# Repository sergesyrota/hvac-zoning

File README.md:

# HVAC Zoning

System to segment single hvac unit into multiple zones

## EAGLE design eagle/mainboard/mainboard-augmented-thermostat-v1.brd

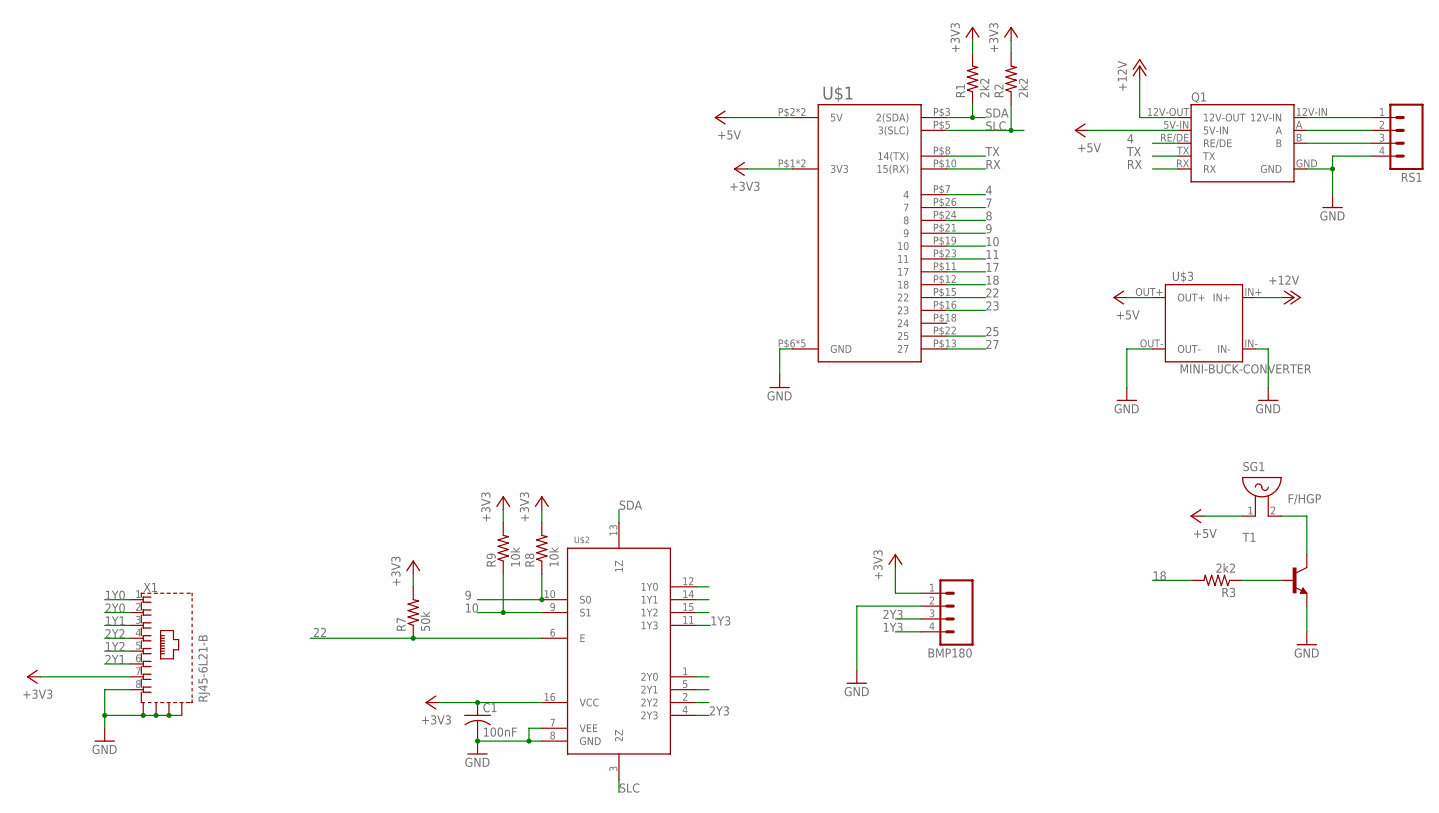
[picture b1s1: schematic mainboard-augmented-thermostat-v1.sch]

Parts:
BMP180: M04; 04P
C1: 100nF; C0603K
Q1: RS485-ADAPTER0.05-CONNECTOR; RS485-ADAPTOR-05
R1, R2, R3: 2k2; R0603
R7: 50k; R0603
R8, R9: 10k; R0603
RS1: M04; 04P
SG1: F/HGP
T1: BC808-NPN-SOT23-BEC; SOT23-BEC
U$1: RASPI-GPIO; RASPI-GPIO-1
U$2: 74HC4052SO-16; SO16
U$3: MINI-BUCK-CONVERTER
X1: RJ45-6L21-B; RJ45-SHIELD1

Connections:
1Y0: U$2.12 (1Y0), X1.1
1Y1: U$2.14 (1Y1), X1.3
1Y2: U$2.15 (1Y2), X1.5
1Y3: BMP180.4, U$2.11 (1Y3)
2Y0: U$2.1 (2Y0), X1.2
2Y1: U$2.5 (2Y1), X1.6
2Y2: U$2.2 (2Y2), X1.4
2Y3: BMP180.3, U$2.4 (2Y3)
4: Q1.RE/DE, U$1.P$7 (4)
7: U$1.P$26 (7)
8: U$1.P$24 (8)
9: R8.1, U$1.P$21 (9), U$2.10 (S0)
10: R9.1, U$1.P$19 (10), U$2.9 (S1)
11: U$1.P$23 (11)
17: U$1.P$11 (17)
18: R3.2, U$1.P$12 (18)
22: R7.1, U$1.P$15 (22), U$2.6 (E)
23: U$1.P$16 (23)
25: U$1.P$22 (25)
27: U$1.P$13 (27)
+3V3: BMP180.1, C1.1, R1.2, R2.2, R7.2, R8.2, R9.2, U$1.P$1 (3V3), U$1.P$17 (3V3), U$2.16 (VCC), X1.7
+5V: Q1.5V-IN, SG1.1, U$1.P$2 (5V), U$1.P$4 (5V), U$3.OUT+
+12V: Q1.12V-OUT, U$3.IN+
GND: BMP180.2, C1.2, Q1.GND, RS1.4, T1.E, U$1.P$6 (GND), U$1.P$9 (GND), U$1.P$14 (GND), U$1.P$20 (GND), U$1.P$25 (GND), U$2.7 (VEE), U$2.8 (GND), U$3.IN-, U$3.OUT-, X1.8, X1.S1 (S), X1.S2 (S), X1.S3 (S), X1.S4 (S)
unnamed: R3.1, T1.B
unnamed: SG1.2, T1.C
RS-12V: Q1.12V-IN, RS1.1
RS-A: Q1.A, RS1.2
RS-B: Q1.B, RS1.3
RX: Q1.RX, U$1.P$10 (15(RX))
SDA: R1.1, U$1.P$3 (2(SDA)), U$2.13 (1Z)
SLC: R2.1, U$1.P$5 (3(SLC)), U$2.3 (2Z)
TX: Q1.TX, U$1.P$8 (14(TX))

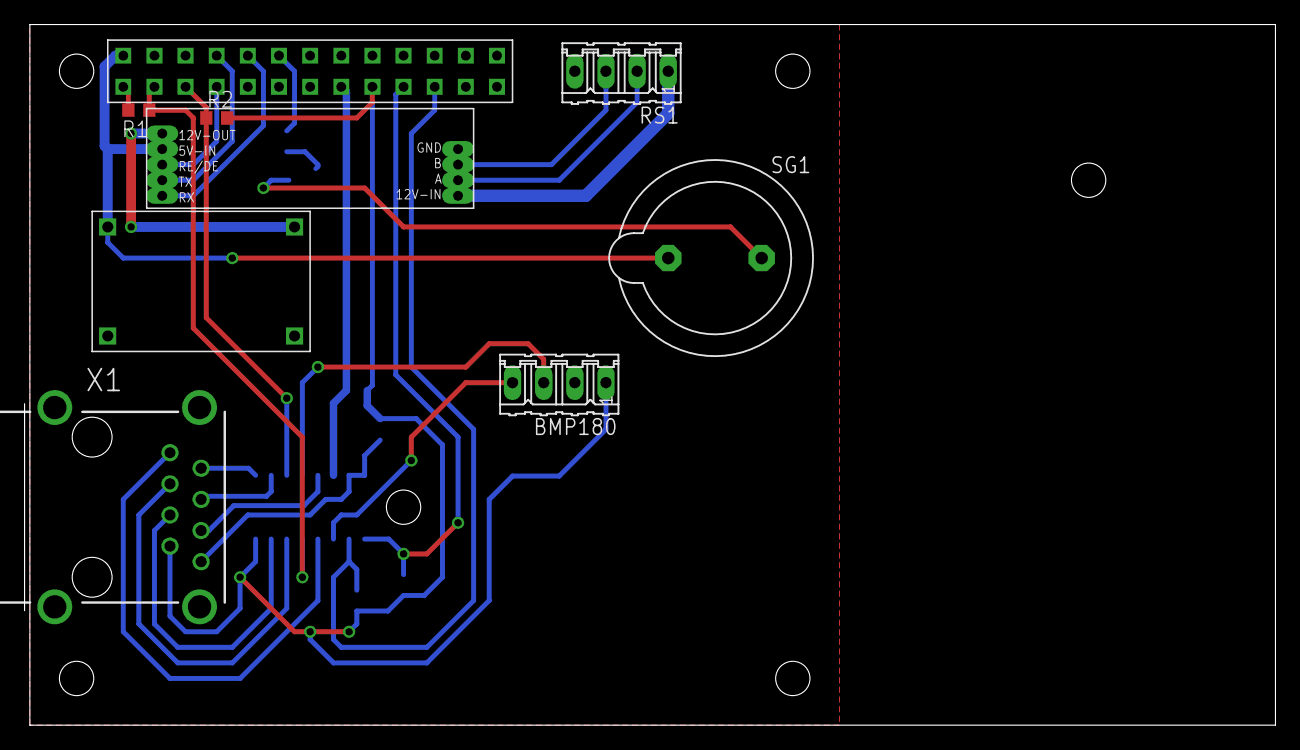
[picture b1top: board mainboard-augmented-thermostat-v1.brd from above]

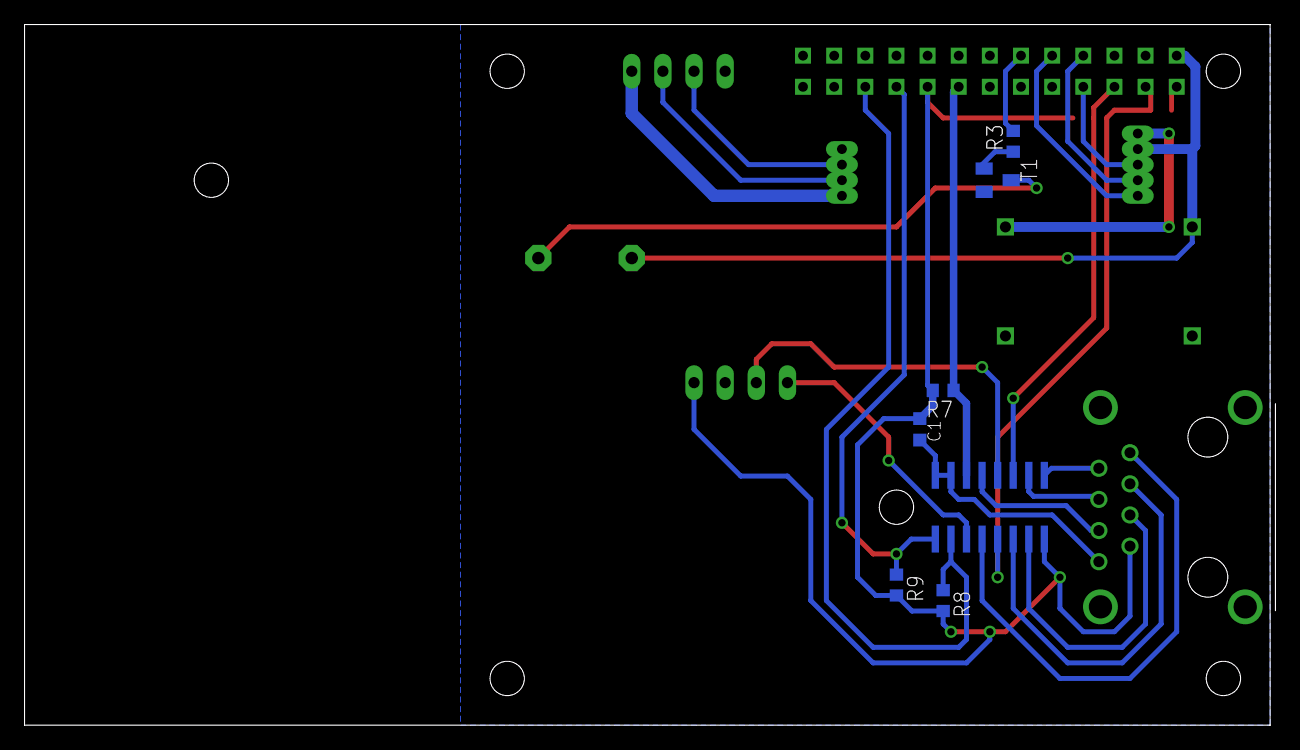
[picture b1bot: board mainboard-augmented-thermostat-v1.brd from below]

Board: 2 copper layers, 102.0 x 57.1 mm, 16 parts (7 on the bottom side), 26 nets.

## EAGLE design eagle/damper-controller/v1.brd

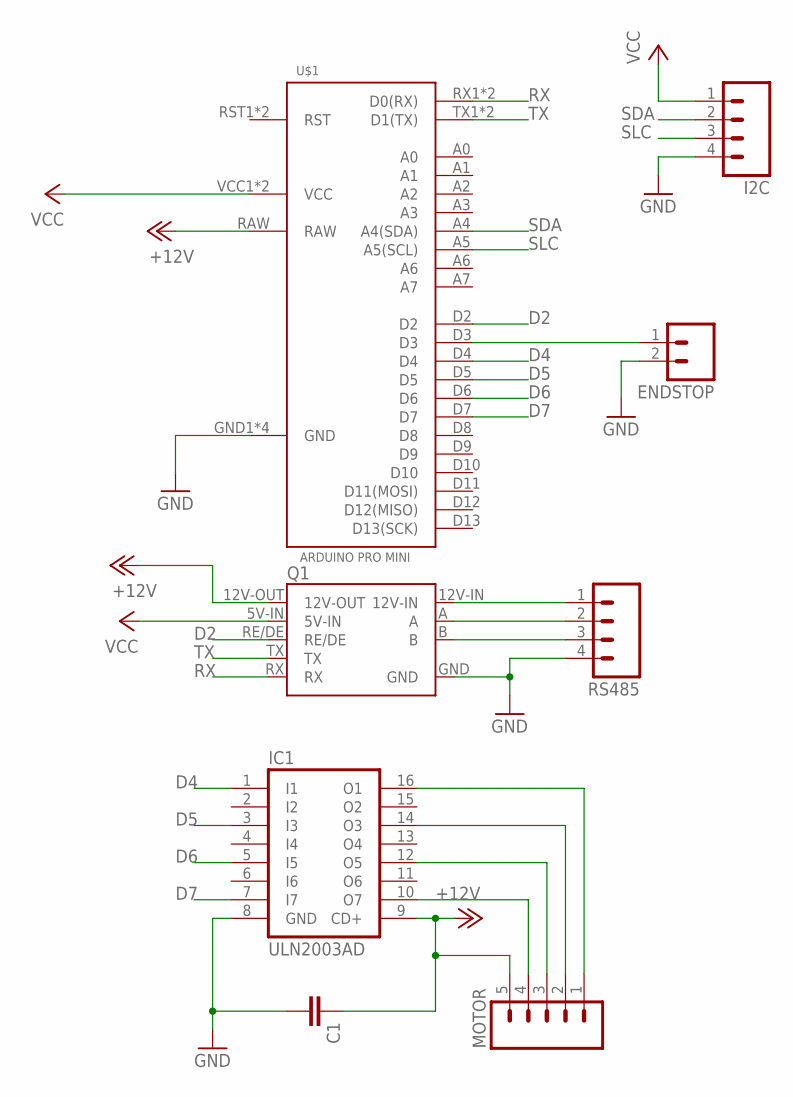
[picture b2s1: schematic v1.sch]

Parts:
C1: CC0603; C0603
ENDSTOP: M02; 02P
I2C: M04; 04P
IC1: ULN2003AD; SO16
MOTOR: M05; 05P
Q1: RS485-ADAPTER0.05-CONNECTOR; RS485-ADAPTOR-05
RS485: M04; 04P
U$1: ARDUINO-PRO-MINI

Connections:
+12V: C1.1, IC1.9 (CD+), MOTOR.5, Q1.12V-OUT, U$1.RAW
D2: Q1.RE/DE, U$1.D2
D4: IC1.1 (I1), U$1.D4
D5: IC1.3 (I3), U$1.D5
D6: IC1.5 (I5), U$1.D6
D7: IC1.7 (I7), U$1.D7
GND: C1.2, ENDSTOP.2, I2C.4, IC1.8 (GND), Q1.GND, RS485.4, U$1.GND1 (GND), U$1.GND2 (GND), U$1.GND3 (GND), U$1.GND4 (GND)
unnamed: Q1.12V-IN, RS485.1
unnamed: IC1.16 (O1), MOTOR.1
unnamed: IC1.14 (O3), MOTOR.2
unnamed: IC1.12 (O5), MOTOR.3
unnamed: IC1.10 (O7), MOTOR.4
unnamed: Q1.A, RS485.2
unnamed: Q1.B, RS485.3
unnamed: ENDSTOP.1, U$1.D3
RX: Q1.RX, U$1.RX1 (D0(RX)), U$1.RX2 (D0(RX))
SDA: I2C.2, U$1.A4 (A4(SDA))
SLC: I2C.3, U$1.A5 (A5(SCL))
TX: Q1.TX, U$1.TX1 (D1(TX)), U$1.TX2 (D1(TX))
VCC: I2C.1, Q1.5V-IN, U$1.VCC1 (VCC), U$1.VCC2 (VCC)

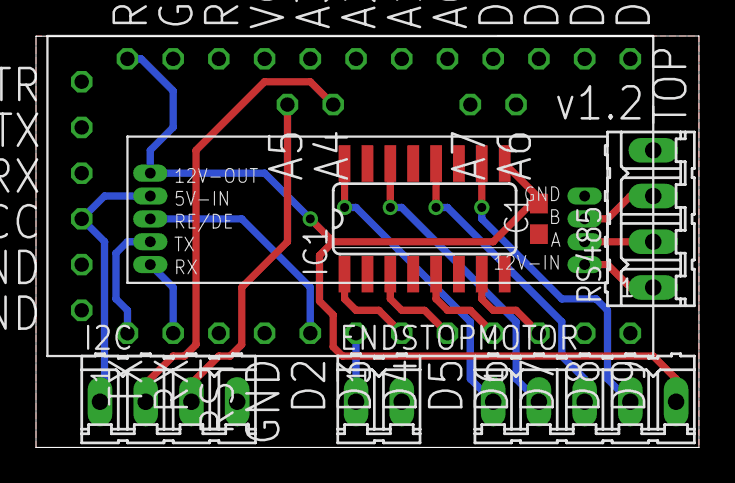
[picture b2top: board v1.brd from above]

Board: 2 copper layers, 36.8 x 22.9 mm, 8 parts (0 on the bottom side), 20 nets.

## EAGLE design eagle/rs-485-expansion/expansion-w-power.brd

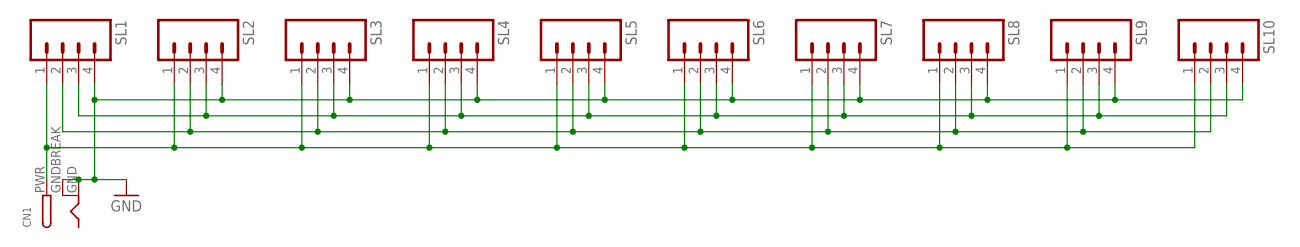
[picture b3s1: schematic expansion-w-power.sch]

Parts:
CN1: DCBARRELPTH; DCJACK_2MM_PTH
SL1, SL2, SL3, SL4, SL5, SL6, SL7, SL8, SL9, SL10: M04; 04P

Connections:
GND: CN1.GND, CN1.GNDBREAK, SL1.4, SL2.4, SL3.4, SL4.4, SL5.4, SL6.4, SL7.4, SL8.4, SL9.4, SL10.4
unnamed: SL1.3, SL2.3, SL3.3, SL4.3, SL5.3, SL6.3, SL7.3, SL8.3, SL9.3, SL10.3
unnamed: SL1.2, SL2.2, SL3.2, SL4.2, SL5.2, SL6.2, SL7.2, SL8.2, SL9.2, SL10.2
unnamed: CN1.PWR, SL1.1, SL2.1, SL3.1, SL4.1, SL5.1, SL6.1, SL7.1, SL8.1, SL9.1, SL10.1

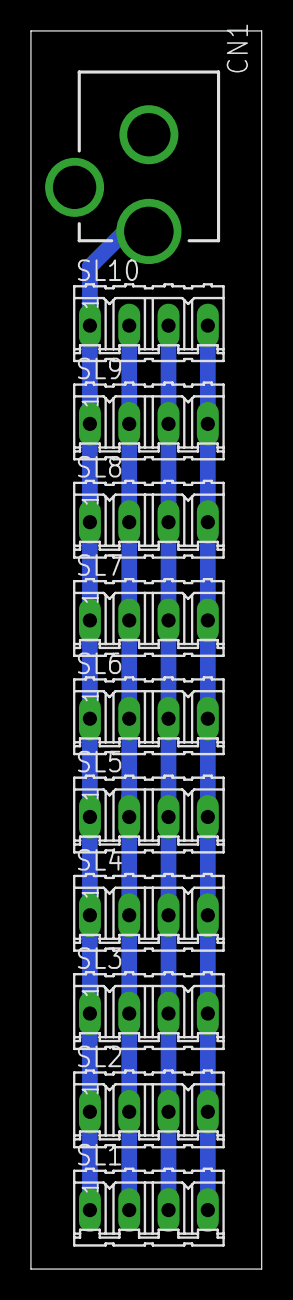
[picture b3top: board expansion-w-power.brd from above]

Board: 2 copper layers, 14.9 x 80.0 mm, 11 parts (0 on the bottom side), 4 nets.

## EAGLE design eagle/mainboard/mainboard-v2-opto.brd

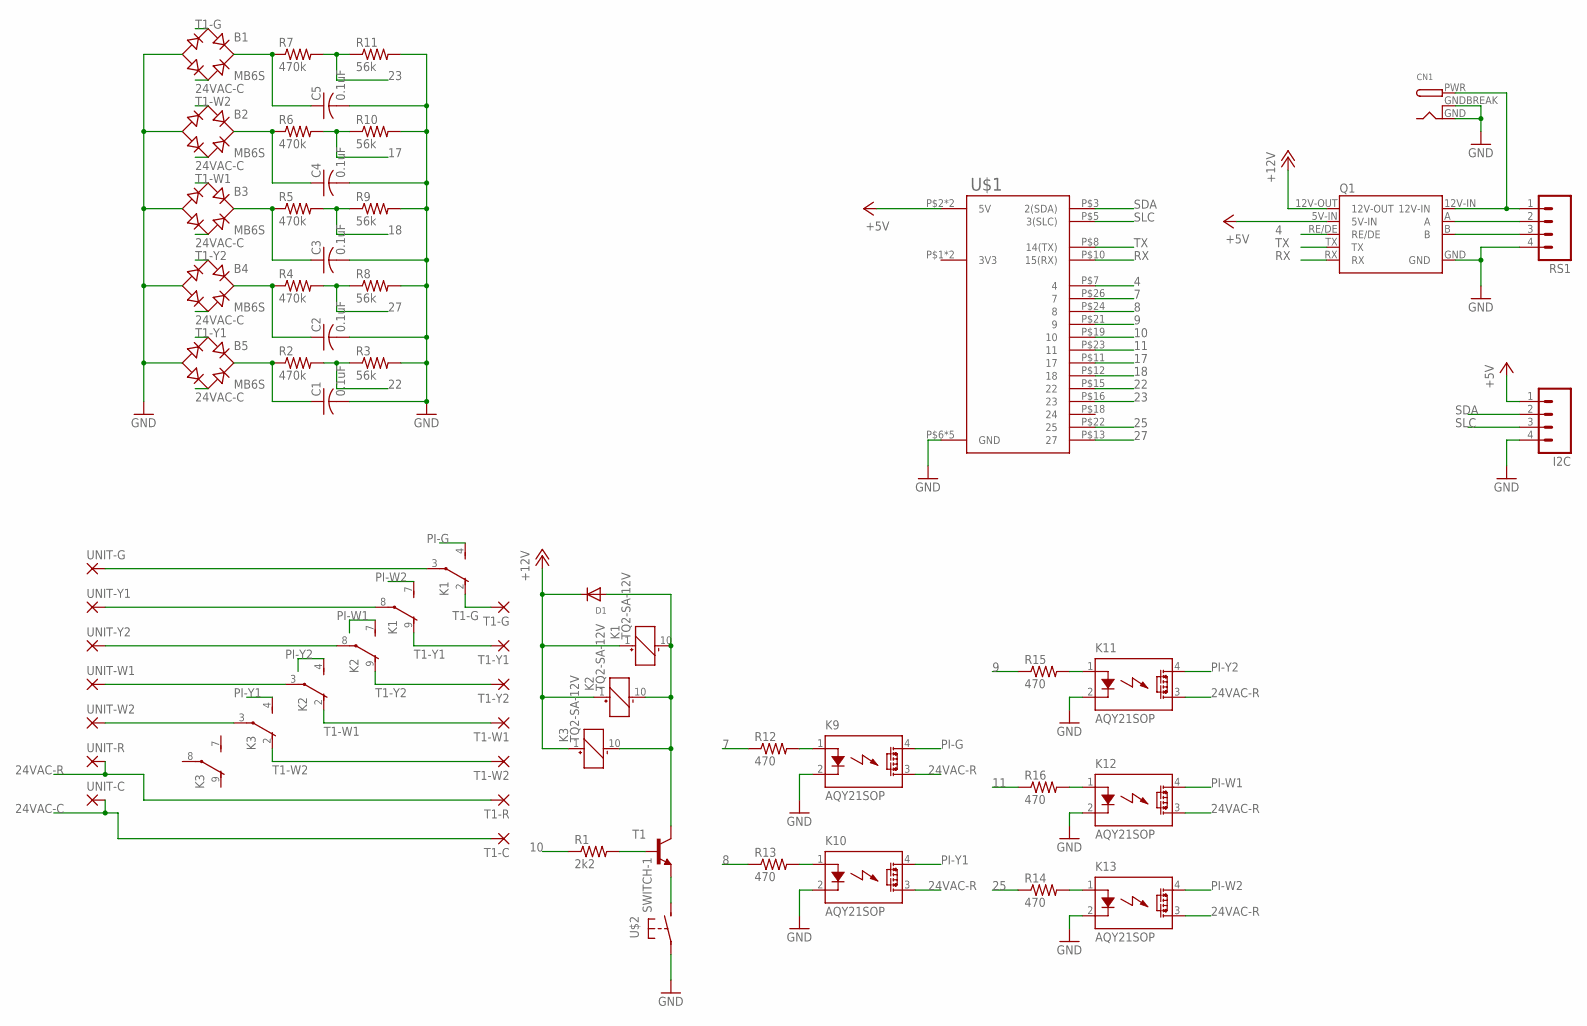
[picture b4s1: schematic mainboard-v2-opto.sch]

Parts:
B1, B2, B3, B4, B5: MB6S; SOIC-4
C1, C2, C3, C4, C5: 0.1uF; C0603
CN1: DCBARRELPTH; DCJACK_2MM_PTH
D1: DIODESMA; SMADIODE
I2C: M04; 04P
K1, K2, K3: TQ2-SA-12V; TQ-SA
K9, K10, K11, K12, K13: AQY21SOP; SOP04
Q1: RS485-ADAPTER0.05-CONNECTOR; RS485-ADAPTOR-05
R1: 2k2; R0603
R2, R4, R5, R6, R7: 470k; R0603
R3, R8, R9, R10, R11: 56k; R0603
R12, R13, R14, R15, R16: 470; R0603
RS1: M04; 04P
T1: BC808-NPN-SOT23-BEC; SOT23-BEC
T1-C, T1-G, T1-R, T1-W1, T1-W2, T1-Y1, T1-Y2: 2,15/1,0
U$1: RASPI-GPIO; RASPI-GPIO-1
U$2: SWITCH-1
UNIT-C: 2,15/1,0
UNIT-G: 2,15/1,0
UNIT-R: 2,15/1,0
UNIT-W1, UNIT-W2: 2,15/1,0
UNIT-Y1, UNIT-Y2: 2,15/1,0

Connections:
3V3: U$1.P$1 (3V3), U$1.P$17 (3V3)
4: Q1.RE/DE, U$1.P$7 (4)
7: R12.1, U$1.P$26 (7)
8: R13.1, U$1.P$24 (8)
9: R15.1, U$1.P$21 (9)
10: R1.1, U$1.P$19 (10)
11: R16.1, U$1.P$23 (11)
17: R6.2, R10.1, U$1.P$11 (17)
18: R5.2, R9.1, U$1.P$12 (18)
22: R2.2, R3.1, U$1.P$15 (22)
23: R7.2, R11.1, U$1.P$16 (23)
24VAC-C: B1.~2 (AC2), B2.~2 (AC2), B3.~2 (AC2), B4.~2 (AC2), B5.~2 (AC2), T1-C.1, UNIT-C.1
24VAC-R: K9.3 (DS2), K10.3 (DS2), K11.3 (DS2), K12.3 (DS2), K13.3 (DS2), T1-R.1, UNIT-R.1
25: R14.1, U$1.P$22 (25)
27: R4.2, R8.1, U$1.P$13 (27)
+5V: I2C.1, Q1.5V-IN, U$1.P$2 (5V), U$1.P$4 (5V)
+12V: D1.C, K1.1 (+), K2.1 (+), K3.1 (+), Q1.12V-OUT
GND: B1.-, B2.-, B3.-, B4.-, B5.-, C1.2, C2.2, C3.2, C4.2, C5.2, CN1.GND, CN1.GNDBREAK, I2C.4, K9.2 (K), K10.2 (K), K11.2 (K), K12.2 (K), K13.2 (K), Q1.GND, R3.2, R8.2, R9.2, R10.2, R11.2, RS1.4, U$1.P$6 (GND), U$1.P$9 (GND), U$1.P$14 (GND), U$1.P$20 (GND), U$1.P$25 (GND), U$2.P$1
unnamed: B5.+, C1.1, R2.1
unnamed: K1.3, UNIT-G.1
unnamed: K1.8, UNIT-Y1.1
unnamed: K2.8, UNIT-Y2.1
unnamed: D1.A, K1.10 (-), K2.10 (-), K3.10 (-), T1.C
unnamed: R1.2, T1.B
unnamed: K2.3, UNIT-W1.1
unnamed: K13.1 (A), R14.2
unnamed: K3.3, UNIT-W2.1
unnamed: B1.+, C5.1, R7.1
unnamed: K12.1 (A), R16.2
unnamed: K11.1 (A), R15.2
unnamed: B4.+, C2.1, R4.1
unnamed: B3.+, C3.1, R5.1
unnamed: T1.E, U$2.P$2 (S)
unnamed: K9.1 (A), R12.2
unnamed: K10.1 (A), R13.2
unnamed: B2.+, C4.1, R6.1
PI-G: K1.4 (S), K9.4 (DS1)
PI-W1: K2.7 (S), K12.4 (DS1)
PI-W2: K1.7 (S), K13.4 (DS1)
PI-Y1: K3.4 (S), K10.4 (DS1)
PI-Y2: K2.4 (S), K11.4 (DS1)
RS-12V: CN1.PWR, Q1.12V-IN, RS1.1
RS-A: Q1.A, RS1.2
RS-B: Q1.B, RS1.3
RX: Q1.RX, U$1.P$10 (15(RX))
SDA: I2C.2, U$1.P$3 (2(SDA))
SLC: I2C.3, U$1.P$5 (3(SLC))
T1-G: B1.~1 (AC1), K1.2 (O), T1-G.1
T1-W1: B3.~1 (AC1), K2.2 (O), T1-W1.1
T1-W2: B2.~1 (AC1), K3.2 (O), T1-W2.1
T1-Y1: B5.~1 (AC1), K1.9 (O), T1-Y1.1
T1-Y2: B4.~1 (AC1), K2.9 (O), T1-Y2.1
TX: Q1.TX, U$1.P$8 (14(TX))

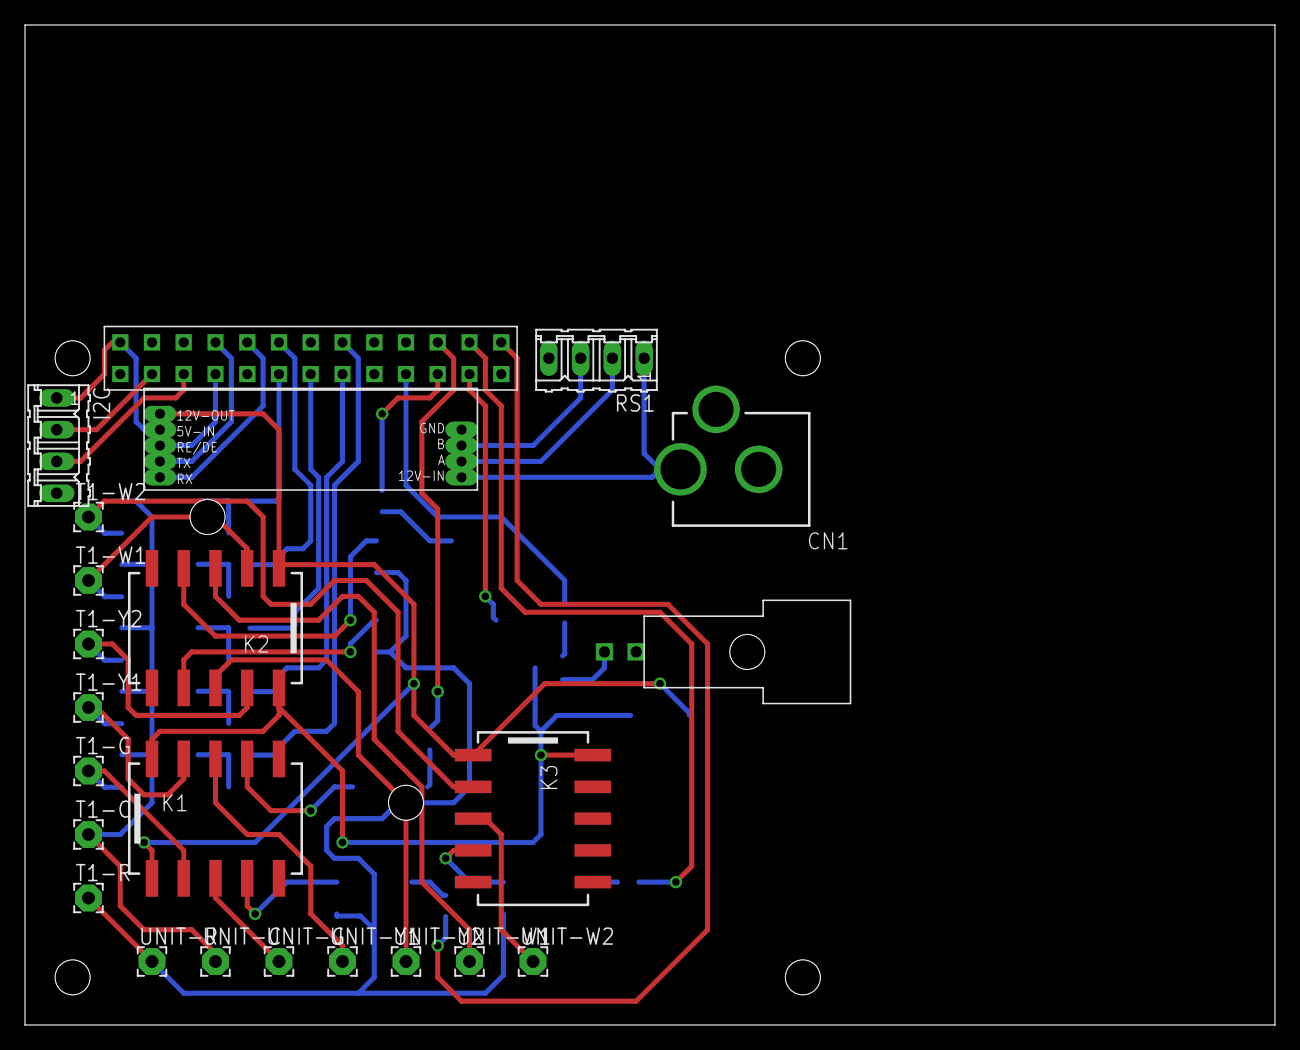
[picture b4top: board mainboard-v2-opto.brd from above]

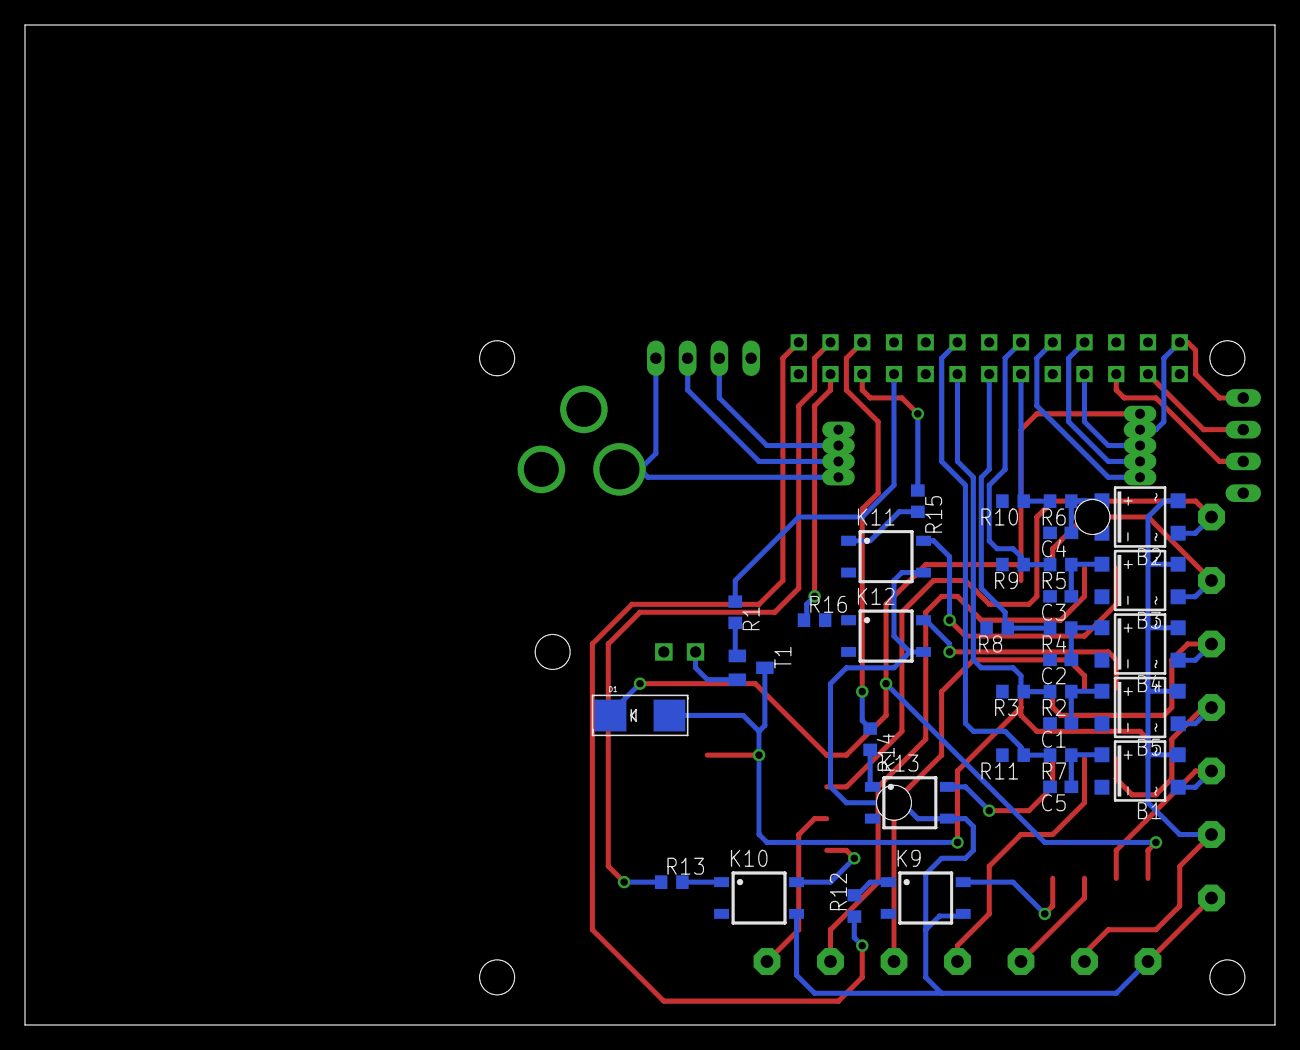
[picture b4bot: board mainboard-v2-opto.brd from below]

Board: 2 copper layers, 100.0 x 80.0 mm, 56 parts (33 on the bottom side), 53 nets.

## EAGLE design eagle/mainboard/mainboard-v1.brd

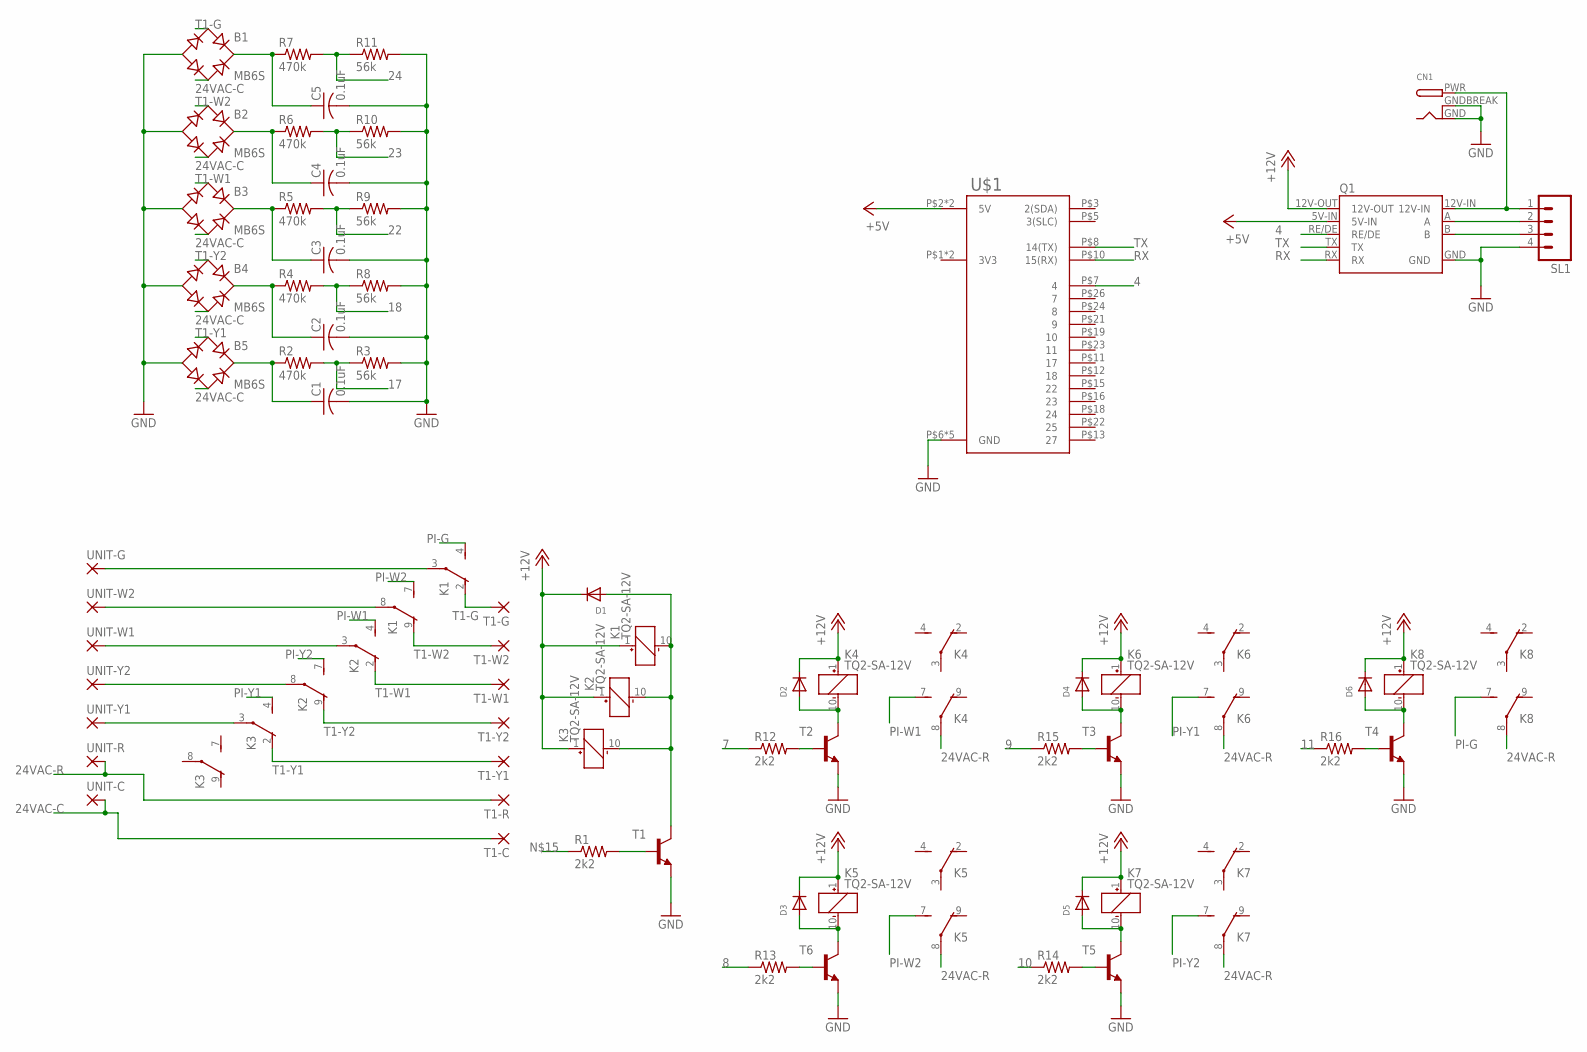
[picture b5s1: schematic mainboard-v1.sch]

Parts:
B1, B2, B3, B4, B5: MB6S; SOIC-4
C1, C2, C3, C4, C5: 0.1uF; C0603
CN1: DCBARRELPTH; DCJACK_2MM_PTH
D1, D2, D3, D4, D5, D6: DIODESMA; SMADIODE
K1, K2, K3, K4, K5, K6, K7, K8: TQ2-SA-12V; TQ-SA
Q1: RS485-ADAPTER0.05-CONNECTOR; RS485-ADAPTOR-05
R1, R12, R13, R14, R15, R16: 2k2; R0603
R2, R4, R5, R6, R7: 470k; R0603
R3, R8, R9, R10, R11: 56k; R0603
SL1: M04; 04P
T1, T2, T3, T4, T5, T6: BC808-NPN-SOT23-BEC; SOT23-BEC
T1-C, T1-G, T1-R, T1-W1, T1-W2, T1-Y1, T1-Y2: 1,6/0,9
U$1: RASPI-GPIO; RASPI-GPIO-1
UNIT-C: 1,6/0,9
UNIT-G: 1,6/0,9
UNIT-R: 1,6/0,9
UNIT-W1, UNIT-W2: 1,6/0,9
UNIT-Y1, UNIT-Y2: 1,6/0,9

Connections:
3V3: U$1.P$1 (3V3), U$1.P$17 (3V3)
4: Q1.RE/DE, U$1.P$7 (4)
7: R12.1
8: R13.1
9: R15.1
10: R14.1
11: R16.1
17: R2.2, R3.1
18: R4.2, R8.1
22: R5.2, R9.1
23: R6.2, R10.1
24: R7.2, R11.1
24VAC-C: B1.~2 (AC2), B2.~2 (AC2), B3.~2 (AC2), B4.~2 (AC2), B5.~2 (AC2), T1-C.1, UNIT-C.1
24VAC-R: K4.8, K5.8, K6.8, K7.8, K8.8, T1-R.1, UNIT-R.1
+5V: Q1.5V-IN, U$1.P$2 (5V), U$1.P$4 (5V)
+12V: D1.C, D2.C, D3.C, D4.C, D5.C, D6.C, K1.1 (+), K2.1 (+), K3.1 (+), K4.1 (+), K5.1 (+), K6.1 (+), K7.1 (+), K8.1 (+), Q1.12V-OUT
GND: B1.-, B2.-, B3.-, B4.-, B5.-, C1.2, C2.2, C3.2, C4.2, C5.2, CN1.GND, CN1.GNDBREAK, Q1.GND, R3.2, R8.2, R9.2, R10.2, R11.2, SL1.4, T1.E, T2.E, T3.E, T4.E, T5.E, T6.E, U$1.P$6 (GND), U$1.P$9 (GND), U$1.P$14 (GND), U$1.P$20 (GND), U$1.P$25 (GND)
unnamed: B5.+, C1.1, R2.1
unnamed: K1.3, UNIT-G.1
unnamed: K1.8, UNIT-W2.1
unnamed: D1.A, K1.10 (-), K2.10 (-), K3.10 (-), T1.C
unnamed: R1.2, T1.B
unnamed: K3.3, UNIT-Y1.1
unnamed: K2.8, UNIT-Y2.1
unnamed: K2.3, UNIT-W1.1
unnamed: B1.+, C5.1, R7.1
unnamed: B4.+, C2.1, R4.1
unnamed: B3.+, C3.1, R5.1
unnamed: B2.+, C4.1, R6.1
unnamed: CN1.PWR, Q1.12V-IN, SL1.1
unnamed: D2.A, K4.10 (-), T2.C
unnamed: Q1.A, SL1.2
unnamed: Q1.B, SL1.3
unnamed: D3.A, K5.10 (-), T6.C
unnamed: D5.A, K7.10 (-), T5.C
unnamed: D4.A, K6.10 (-), T3.C
unnamed: D6.A, K8.10 (-), T4.C
unnamed: R13.2, T6.B
unnamed: R12.2, T2.B
unnamed: R15.2, T3.B
unnamed: R14.2, T5.B
unnamed: R16.2, T4.B
PI-G: K1.4 (S), K8.7 (S)
PI-W1: K2.4 (S), K4.7 (S)
PI-W2: K1.7 (S), K5.7 (S)
PI-Y1: K3.4 (S), K6.7 (S)
PI-Y2: K2.7 (S), K7.7 (S)
RX: Q1.RX, U$1.P$10 (15(RX))
T1-G: B1.~1 (AC1), K1.2 (O), T1-G.1
T1-W1: B3.~1 (AC1), K2.2 (O), T1-W1.1
T1-W2: B2.~1 (AC1), K1.9 (O), T1-W2.1
T1-Y1: B5.~1 (AC1), K3.2 (O), T1-Y1.1
T1-Y2: B4.~1 (AC1), K2.9 (O), T1-Y2.1
TX: Q1.TX, U$1.P$8 (14(TX))

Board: 2 copper layers, 64 parts (0 on the bottom side), 49 nets, no tracks yet.

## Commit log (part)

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2016-02-09 Added link to RS-485 module, and adjusted readme tiny bit.
2016-02-09 Clarification on rs-485 module version file
2016-02-10 First version of damper controller board.
2016-02-10 Adding models for opposite ends vent mark tool and stepper mount adaptor.
2016-03-06 Finished damper controller, and modified for OSH Park print, instead of home-made method
2016-03-13 Adjusting motor shaft model further
2016-03-13 Adjusting damper controller board based on first prototype of PCB. Needed to move switch connector, and removed LED, as there is no space.
2016-03-13 Starting work on mainboard. Too many relays!
2016-03-15 Starting work on solid state relay version of mainboard, as it's much more manageable (albeit still painful)
2016-03-15 Updating gitignore with lock filw
2016-03-16 Really close to finishing first prototype of the motherboard.
2016-03-20 Added different spin on mainboard: one that will augment existing wifi thermostat, rather than take over control.
2016-03-20 Added RS485 10-connector expansion board, with power input.
2016-03-20 Created blank Eagle project for environment sensor.
2016-03-20 Added header file for MiniStepper library to start development.
2016-03-22 Starting to develop mini stepper library.
2016-03-29 Finished MiniStepper library implementation. In experiments, seems like max RPM is somewhere between 20 and 30. Would be nice to implement acceleration feature next.
2016-03-29 Finished implementing MiniStepper library with addition of going to a specific degree, rather than having to calculate number of steps externally.
2016-04-06 Added ability to get current position to mini stepper library
2016-04-06 Adding vent firmware. Tested with real hardware. Default parameters should be good enough.
2016-04-06 Tried adding CPU mount to vent bracket, did not work out. Adjusted positioning of a switch a bit, though.
2016-04-06 Adding CPU enclosure 3d model
2016-04-13 Rudimentary environment sensor to begin testing.
2016-04-13 Added BMP160 mount model
2016-04-13 Added variable to have square duct mount adaptor, instead of round
2016-04-13 Moving config include at the bottom of all includes
2016-04-13 Adjusted damper controller so that connectors have enough clearence, and added text to indicate version.
2016-04-13 Added fourth DMP180 sensor, right on the mainboard, so that we can compare to ambient pressure, if we need to.
2016-04-13 Adding a rudimentary controller for this first hack for now.
2016-04-13 Cleaning up some garbage
2016-04-29 Adding middle vents to bedroom schedule, and adjusting temps a bit.
2016-04-30 Added buzzer to the mainboard. Ready for first prototype!
2016-12-04 Vent adaptor fixes
2016-12-04 Adjusted temporary implementation of controller, scheduling, etc.
2016-12-04 Fixing environment sensor JSON string
2016-12-06 Adding calibration possibility to the environment sensor
2017-01-29 adjusting schedule, and moving to F rather than C
2017-01-30 Adding silex skeleton application and starting server development
2017-05-19 Implementing guest bedroom temperature control.
2017-08-12 WIP commit
2017-08-12 Adding middle tstat caching
2017-08-12 Enabling guest vents back
2017-11-27 Adding API app, starting with Docker runtime environment.
2017-12-06 Creating base SYmfony 4 applicaiton, and updating docker container with dependencies.
2018-01-29 Adding another implementation, one that is simple, and relies on external apps to gather information needed for decision making.
2018-01-29 Besic separate implementation of thermostat that works off of a CLI, and a static json file with schedule.
2018-01-30 Added south bedroom thermostat implementation
2018-01-30 Committing work in progress on Symfony 4 based implementation (for now abandoned)
2018-01-30 Added exception in cli thermostat adapter
2018-01-30 Implemented minimum airflow enforcement when manipulating vents.
2018-01-30 typo
2018-02-19 Moving env to example.
2018-02-19 Added NEST API adapter for thermostat. @todo: caching layer for NEST, consider streaming?
2018-02-19 Added leaving all vents open if system is neither actively heating nor cooling.
2018-02-19 Added some readme, and my modifications to bedroom configuration
2018-02-19 Added exception when nest thermostat is offline.
2018-02-20 Added RS485v1 adapter for vents
2018-02-20 Added a delay between vent move execution (useful if all vents are on the same power source, which might not have enough juice to drive all motors at the same time)
2018-02-20 Adjusting vent names in the zone configuration file
2018-02-20 adjusting .gitignore, and adding composer lock
2018-02-20 Added actual sensor implementations for temperature sensors for CLI thermostats.
2018-02-20 Removing debug output from rs485 implementation
2018-02-20 Fixing getenv using unquoted text
2018-02-20 Fixing bugs with variable names
2018-02-20 Removing debug output from south temp probe.
2018-02-20 Removing debug output from app
2018-02-20 Adding file cache for nest adapter, this will make sure even multiple thermostats on the same token will have to call API only once.
2018-02-23 Adding Monolog, and a few debug messages.
2018-03-03 Fixing relative path bug.
2018-03-04 Added phpunit; refactored thermostat to conform to PSR-4; Added thermostat adapters autoload; refactored thermostat adapters to remove connection provider (to make it testable); Started implementing 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
2018-03-05 adding nest adapter tests, fixing bugs with deltaT implementation
2018-03-08 Starting to work on an ability to set temperature with nest API. Added a bunch of documentation to functions. Refactored curl calls to be able to reuse the function.
2018-03-08 Added ability to set targets for nest thermostat. Added temperature units conversion to delta function. Added bunch of documentation.
2018-03-08 Adding logic to override master if other zones are calling for heat/cool while master is not doing anything.
2018-03-08 Removed bedrooms configuratino file from repository.
2018-03-08 Adding zones folder, where all zone configuration and environment variables should be saved.
2018-03-08 Adjusting zones gitignore
2018-03-08 Accidentally committed commented out state move execution, fixing that. renamed min_airflow to be consistent with json file.
2018-03-11 Implemented setting temperature for NEST thermostat
2018-03-11 Finished override implementation for adjusting other zones.
2018-03-11 Fixing optionality of threshold parameter.
2018-03-11 Clarifying some comments. Removing too verbose ones. Adding info when state file expired.
2018-03-11 Fixing bug with improper cache file suffix
2018-03-11 Fixing a bug that prevented proper hash from being taken for thermostat due to old data (data not refreshed after changing target temperature)
2018-03-12 Adjusted logic for overrides: we won't execute vent moves when we just removed the override, so we're overshooting zone we were placing the override for, rather than master zone. Master will be adjus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
2018-05-31 Added exception when NEST API is unavailable, so that the file is not overwritten.
2019-12-11 Adding going to default position when degrees command has not been called in timeout period (e.g. when controller stops working, this will open up the vent after timeout). Also adding reset function.
2019-12-14 Adding position timeout functionality and reset command
2020-07-26 Adding current state for bedrooms, and ability to reset override status.
2020-07-26 More debugging.
2020-07-26 Mobile friendly bedroom status page
2021-05-01 Adding functionality of default position to allow for constant recirculation mode.
2021-06-29 Adding vent ID log when there is an exception.
2023-01-04 Removed and revoked google secret
2023-05-21 Started homebridge plugin
2023-05-21 Adding Homebridge adapter
2023-06-03 Fixing a bug in factory, and text in Homebridge adapter
2023-06-03 Removing deltaT from interface, as it's not used
2023-06-03 More human readable log messages
2023-06-03 Fixing reference
2023-06-03 Fixing reference again
2023-06-03 Removing Nest from nagios check, as it's deprecated.
2023-06-03 Adjusting floor heat price
2023-06-03 Adjusting gitignore to also keep record of zones, as there are no secrets there.
2023-06-03 Adding logging for setting overrides
2023-06-03 Adding variable for logger
2023-06-03 Adding more logging information on checksum, as it's not working for Homebridge
2023-06-07 Changed vent error handling to move everything to default if any one vent throws an exception.
2023-06-08 Fixed default zone move when there's an exception
2023-06-08 Fixing setting of temperatures with homebridge, as API update is not instanteneous.
2024-08-09 Adding inverting dampers and some debug.
2024-08-09 Adding checking for error with every vent before executing the moves. If we see errors, we will abort everything.
2024-08-09 Adding config variable for checking vent errors, in case we have to fly blind for a bit
2024-08-12 Adding self-healing option if we encounter an error with vents.
2024-08-12 Restricting self-healing to once per 2 hours, in case we have a fully stuck vent that can't do anything.
2024-12-13 Adding vent checking to config
2024-12-14 Adding vent name to the error message when vent move fails.
2024-12-14 putting name by the ID
2025-01-30 Checking that error reporting for vent already exists, to prevent unknown variable exception
2025-03-08 Fixing self-healing handling with array vs object confusion
2025-07-11 improving self-healing
